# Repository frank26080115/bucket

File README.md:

Bucket
======

This is a tool made to transfer and backup photos from a professional camera while in-the-field. Built with a Raspberry Pi 4 (other Pis will work too, it's all just Python code), using Wi-Fi for file transfers and USB disks for file storage, powered by batteries.

The Problem
----

 While on photography trips, I'm running out of storage on my camera's memory cards. They are expensive memory cards and I can't buy too many of them ($400 for 160 GB, and the camera needs two). I don't want to go back to a hotel before clearing out a memory card either.

So the strategy is to wirelessly transfer the files into a cheaper-slower-but-bigger storage device (TB sized USB disks) simultaneously as the camera is shooting. The slower speed should be fine because the transfers will happen during the down-time, when I'm walking around not taking pictures. USB disks at this size typically cost just a bit over $100 (genuine, authentic, non-scam ones) and require USB-3.0 ports.

Once the photos are in the bigger storage device, I can clear the expensive-and-smaller memory cards without going back to a hotel, using in-camera quick-reformat.

This project needs to be done by late June of 2022, my next vacation. (I hope this explains some very weird decisions I've made)

Features
----

Runs as a FTP server for professional cameras to transfer photos into. A redundant copy of the photo is made if 2 USB disks are inserted. (most professional cameras have two card slots for the purpose of having redundancy as well)

Copies photos from SD card if a SD card reader is inserted into a USB port. Or plug in the camera itself (configure it to run in mass storage mode, and disable USB charging).

The file-names for the photos are typically numbered from 0 to 9999. This isn't a lot of photos and rolls over quickly. When a photo is copied, it is automatically renamed with a much longer number that indicates the date it was taken. The date makes every photo file-name unique and can be easily searched-for and sorted.

EXIF data of the photo is checked for the photo's 5-star rating, if it is rated in-camera, then it is automatically marked for keeping.

Performs disk-cloning when multiple USB disks are inserted.

Uses a HTTP server to show an image gallery in a web browser. The user can choose to keep or delete a photo from the web-page. Each photo is checked for where the camera focused on, and a zoomed-in cropped thumbnail is shown to the user showing where the camera focused (which is even cooler since my camera have AI driven bird-eye-detect).

This allows for a very quick decision whether or not an image is in-focus enough to keep. This implementation keeps the file-sizes small for the web-page, but the user can still click into the full resolution file too.

The software keeps track of the numbers in the file-names. If the number sequence skips a number, it might mean a missing photo, the missing number is shown to the user so they can check in the camera what happened. The camera can indicate a failed FTP transfer, but usually it just retries until it works. This is only useful when the camera is setup to transfer-as-you-shoot.

Hardware UX
----

The UI involves a 102x64 OLED screen and 5 buttons. It is very readable in all lighting conditions. The 5 buttons are divided into 2 up/down buttons and 3 action buttons.

The screen shows the most important information, such as the time (which is kind of like a heart-beat), the number of photos transferred, the amount of disk space remaining, etc.

There is a menu that can be accessed, the menu items are navigated with the up/down buttons. From the menu, the user can do things like initiate drive-cloning.

From the menu, the user can quickly check the Wi-Fi AP's credentials, the FTP IP address, and FTP credentials. It can also display the Wi-Fi credentials and HTTP URL as QR codes.

There is a buzzer that buzzes when there's a problem that requires the user's immediate attention, such as a disk running out of space, or if the battery is too low, etc. The user can press a button to acknowledge the problem to turn off the buzzer.

Hat Circuit and 3D Printed Box
----

This is the circuit I designed to go on top of the Raspberry Pi.

A 3D printed box is designed to protect the entire assembly. It is 3D printed in PETG plastic, because this whole thing gets super hot while running, PLA plastic just won't handle it.

The slots in the design are meant for strapping down a small USB SSD. These SSDs can have one or two TB of storage and should be pretty reliable since they use M.2 drives inside.

Software Architecture
----

This is just one massive Python project, spread across several modules. The hardware IO, various servers, and the main application, can all be independently tested. In fact, because Python is very cross-platform, I did most of my testing on Windows with a simulated screen.

The intention is to improve the reliability of this project by making the Raspberry Pi's microSD card read-only. The Python script will scan all mounted disks for a config file when it starts. This way, the user can still specify some parameters without ever writing to the microSD card.

The Python script will also log events and errors to the first available mounted disk.

The Python script is called upon by `/etc/rc.local`.

The library I used for the FTP server is [pyftpdlib](https://pypi.org/project/pyftpdlib/). The server class can be inherited, callback functions can be added, and a lot of the pathing functions had to be overridden.

The UI used a combination of [CircuitPython](https://circuitpython.org/) (and including the adafruit-circuitpython-ssd1306 library), [gpiozero](https://gpiozero.readthedocs.io/), and [Pillow](https://pillow.readthedocs.io/)

The HTTP server used Python's [built-in HTTP server library](https://docs.python.org/3/library/http.server.html). The HTML pages contains some [JQuery](https://jquery.com/) and uses lazy-loading images.

The EXIF related functions I borrowed [ExifTool](https://exiftool.org/), it's a Perl project but I call upon it as a subprocess from within Python.

USB disk auto-mounting is handled by [the usbmount Debian package](https://github.com/rbrito/usbmount/).

Threads
----

This device packs a bunch of features that involve IO against USB drives, and some of those tasks are more important. The software running has many threads that have multiple task queues with varying priorities.

The main thread is the GUI thread, which runs once every 0.2 seconds, giving a frame-rate of 5 FPS on the OLED display. Most of the thread time will be occupied by a very long I2C transaction as the frame-buffer is being sent to the OLED display. Other threads can run during this transfer without any penalty.

The FTP server and HTTP server both run on their own thread without any throttling, managed by their respective Python libraries. FTP is the most important thread. Wireless file transfer is the highest priority transfer, it isn't even queued, it happens immediately.

The other threads are started and stopped as needed: disk-cloner, keeper-copier, thumbnail-generator

The disk-cloner has two queues. The higher priority queue copies a recently wirelessly transferred file to the redundant disk. The lower priority queue copies between drives upon user request.

The keeper-copier slowly analyzes the EXIF data on recently transferred files to find their 5-star rating. Rated files are moved to the "keep" folder. These tasks has lower priority than the disk-cloner, but it also happens immediately if the user clicks the "keep" button on the HTTP server interface.

The thumbnail-generator thread is the lowest priority, but it becomes high priority when a HTTP client is accessing the thumbnails that have not been generating yet.

Power Supply
----

The hat circuit features a DC/DC step-down converter outputting 5V, rated for up to 6A. The input is supposed to come from two 8.4V batteries. The inputs are diode-OR'ed before going into the converter so I can swap one battery out without shutting down the Pi (and more importantly, prevents one battery literally exploding the other one). Each input is also connected to an ADC with a voltage divider in between.

As for the batteries, I decided it would be smart to use the same FZ100 batteries that my cameras use, so I can carry less stuff. I hacked up a dual charger for FZ100 batteries so it became a battery holder. It will still charge the batteries too.

A latching beefy connector is placed on the bottom of the charger, and wired to the battery tabs of the charger. On the Pi's hat is the mating connector.

This charger is attached to the bottom of the Raspberry Pi via LEGO!

I think this whole project draws about under 1A during actual file transfer using USB flash drives, but a bit over 1A when I use a USB-C SSD. Roughly 4 to 5 hours of battery life.

Alternative Implementation
----

The Raspberry Pi 4 is absolutely horrible for a battery powered project, it has zero power saving features, there's no sleep mode, and draws a ton of current even if the whole CPU is halted. This whole project would've made a lot more sense if it was just a smartphone app.

But my phone doesn't have nearly enough internal storage for this project, the USB port on my phone is also very suspect and I don't want to have a USB hub inserted into it during hikes. I recently did a battery swap on my phone because I love it so much and want to use it for a few more years. So I hope you understand why I can't justify buying a 1 terabyte Galaxy S22 Ultra for this project.

I am interested in an Android app implementation of this device though. Contact me if you want to chat about it.

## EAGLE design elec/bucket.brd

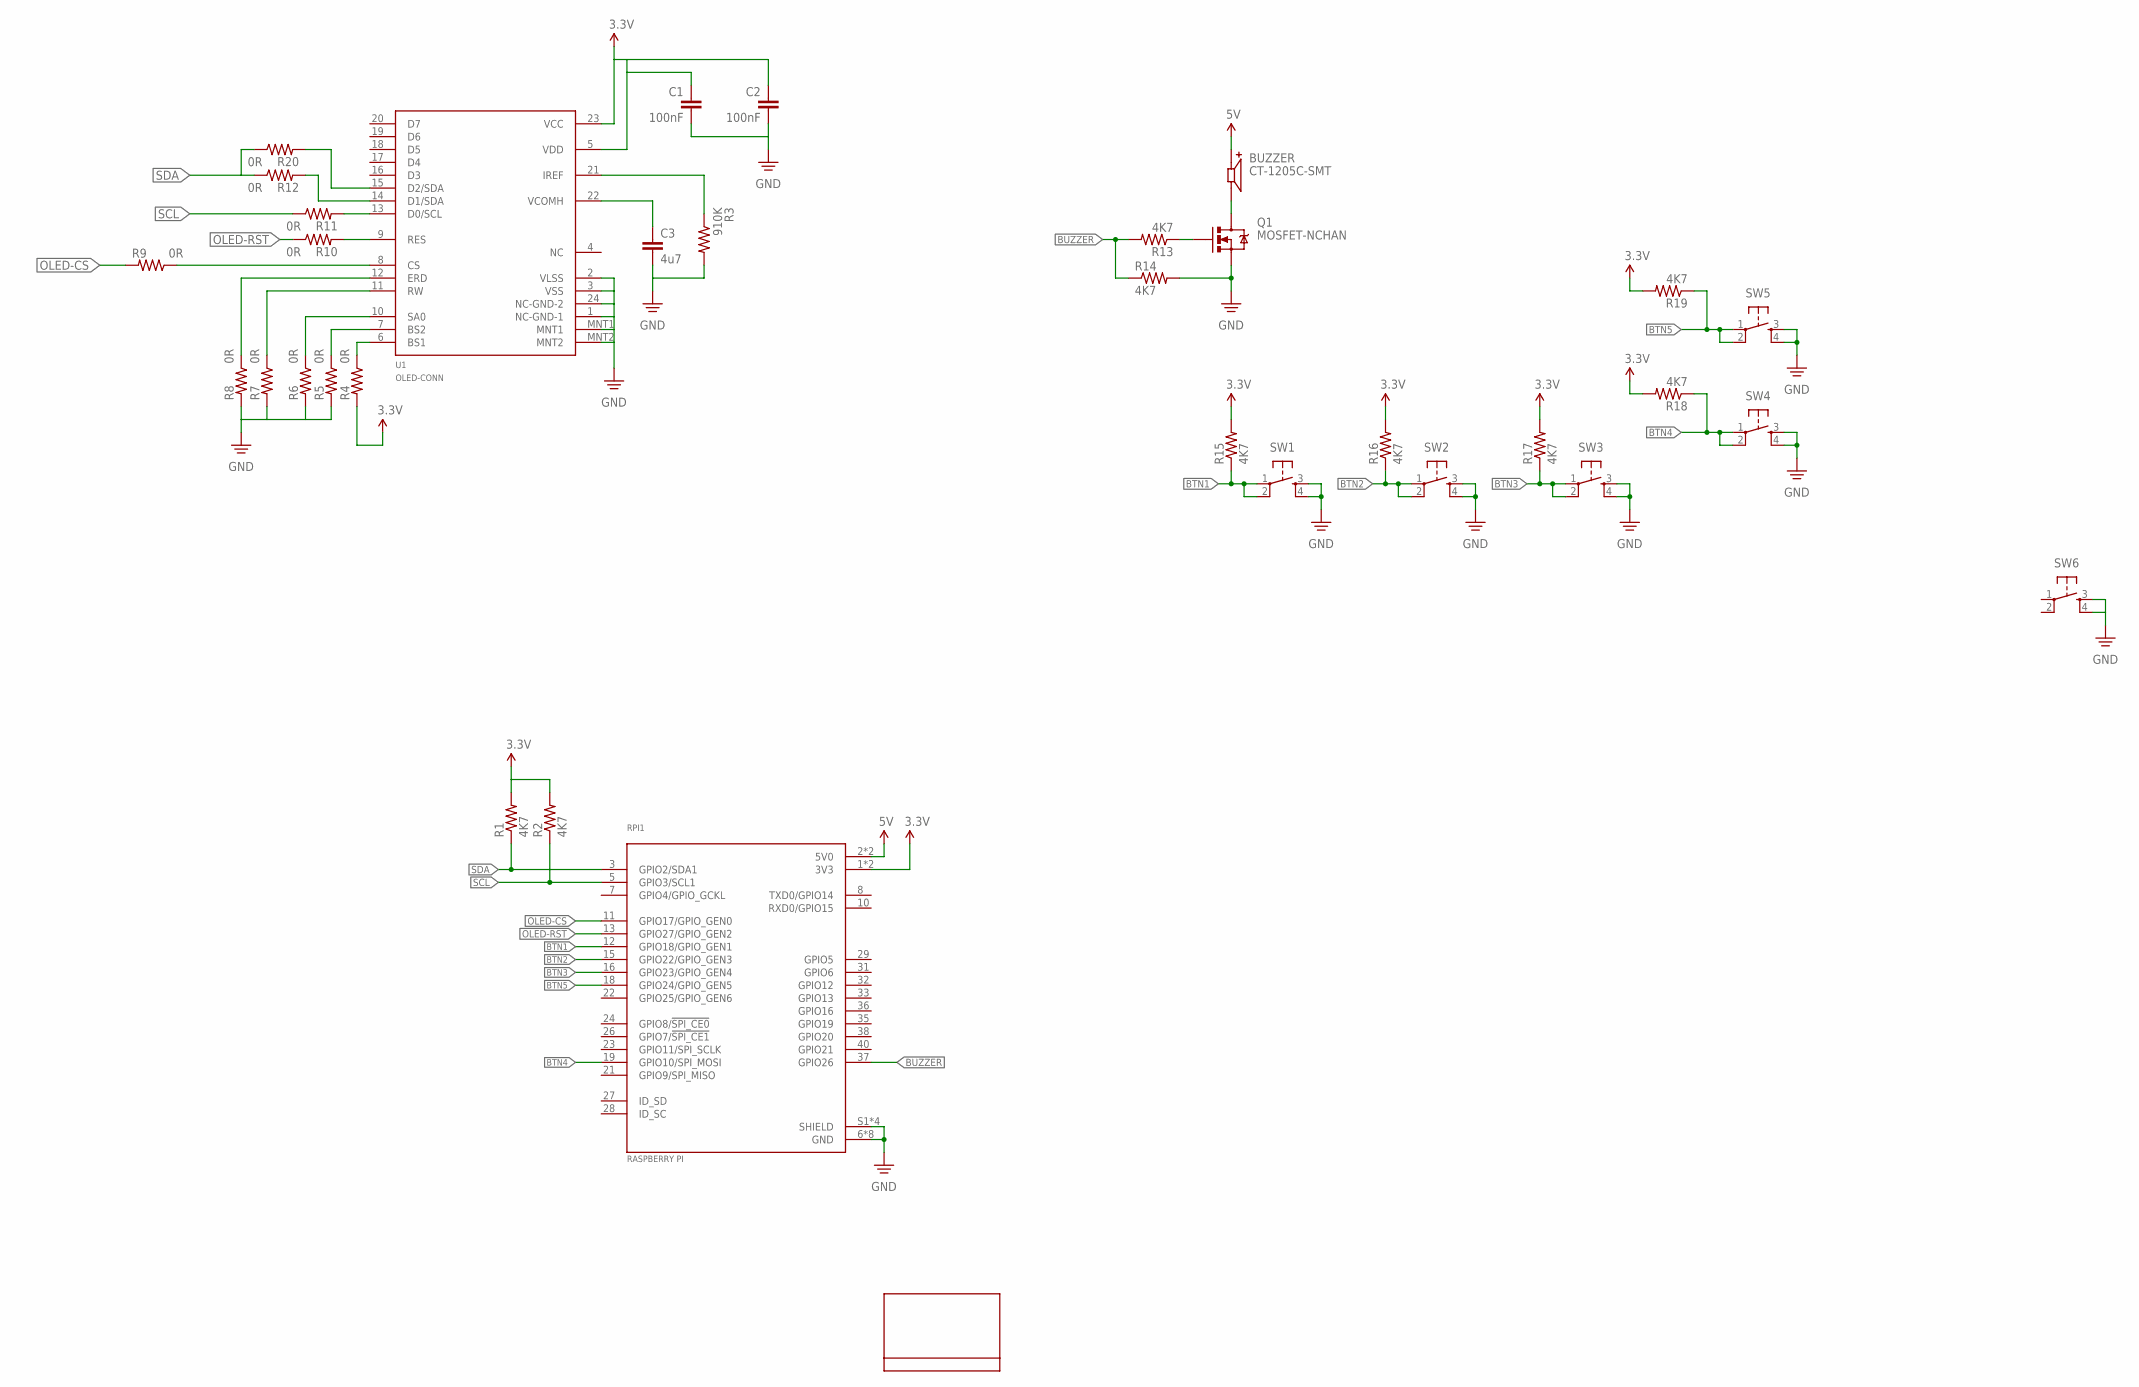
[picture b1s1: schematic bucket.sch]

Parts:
BUZZER: CT-1205C-SMT; CUI_CT-1205C-SMT
C1, C2: 100nF; 0603-CAP
C3: 4u7; 0603-CAP
Q1: MOSFET-NCHAN; SOT23-3
R1, R2, R13, R14, R15, R16, R17, R18, R19: 4K7; 0603-RES
R3: 910K; 0603-RES
R4, R5, R6, R7, R8, R9, R10, R11, R12, R20: 0R; 0603-RES
RPI1: RASPBERRY PI; MODULE_RASPBERRY_PI_3_MODEL_B+
SW1, SW2, SW3, SW4, SW5, SW6: TAC_SWITCHPTH; TACTILE-PTH
U1: OLED-CONN; CONN24_1X24_DRC_FFC_HIR
U$1: OLED-PANEL-1.54IN; OLED-1.54IN

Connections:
3.3V: C1.1, C2.1, R1.2, R2.2, R4.2, R15.2, R16.2, R17.2, R18.2, R19.2, RPI1.1 (3V3), RPI1.17 (3V3), U1.5 (VDD), U1.23 (VCC)
5V: BUZZER.1, RPI1.2 (5V0), RPI1.4 (5V0)
BTN1: R15.1, RPI1.12 (GPIO18/GPIO_GEN1), SW1.1, SW1.2
BTN2: R16.1, RPI1.15 (GPIO22/GPIO_GEN3), SW2.1, SW2.2
BTN3: R17.1, RPI1.16 (GPIO23/GPIO_GEN4), SW3.1, SW3.2
BTN4: R18.1, RPI1.19 (GPIO10/SPI_MOSI), SW4.1, SW4.2
BTN5: R19.1, RPI1.18 (GPIO24/GPIO_GEN5), SW5.1, SW5.2
BUZZER: R13.2, R14.1, RPI1.37 (GPIO26)
GND: C1.2, C2.2, C3.2, Q1.2 (S), R3.2, R5.2, R6.2, R7.2, R8.2, R14.2, RPI1.6 (GND), RPI1.9 (GND), RPI1.14 (GND), RPI1.20 (GND), RPI1.25 (GND), RPI1.30 (GND), RPI1.34 (GND), RPI1.39 (GND), RPI1.S1 (SHIELD), RPI1.S2 (SHIELD), RPI1.S3 (SHIELD), RPI1.S4 (SHIELD), SW1.3, SW1.4, SW2.3, SW2.4, SW3.3, SW3.4, SW4.3, SW4.4, SW5.3, SW5.4, SW6.3, SW6.4, U1.1 (NC-GND-1), U1.2 (VLSS), U1.3 (VSS), U1.24 (NC-GND-2), U1.MNT1, U1.MNT2
unnamed: C3.1, U1.22 (VCOMH)
unnamed: R3.1, U1.21 (IREF)
unnamed: R4.1, U1.6 (BS1)
unnamed: R5.1, U1.7 (BS2)
unnamed: Q1.1 (G), R13.1
unnamed: BUZZER.2, Q1.3 (D)
unnamed: R6.1, U1.10 (SA0)
unnamed: R7.1, U1.11 (RW)
unnamed: R8.1, U1.12 (ERD)
unnamed: R9.1, U1.8 (CS)
unnamed: R10.2, U1.9 (RES)
unnamed: R11.2, U1.13 (D0/SCL)
unnamed: R12.2, U1.14 (D1/SDA)
unnamed: R20.2, U1.15 (D2/SDA)
OLED-CS: R9.2, RPI1.11 (GPIO17/GPIO_GEN0)
OLED-RST: R10.1, RPI1.13 (GPIO27/GPIO_GEN2)
SCL: R2.1, R11.1, RPI1.5 (GPIO3/SCL1)
SDA: R1.1, R12.1, R20.1, RPI1.3 (GPIO2/SDA1)

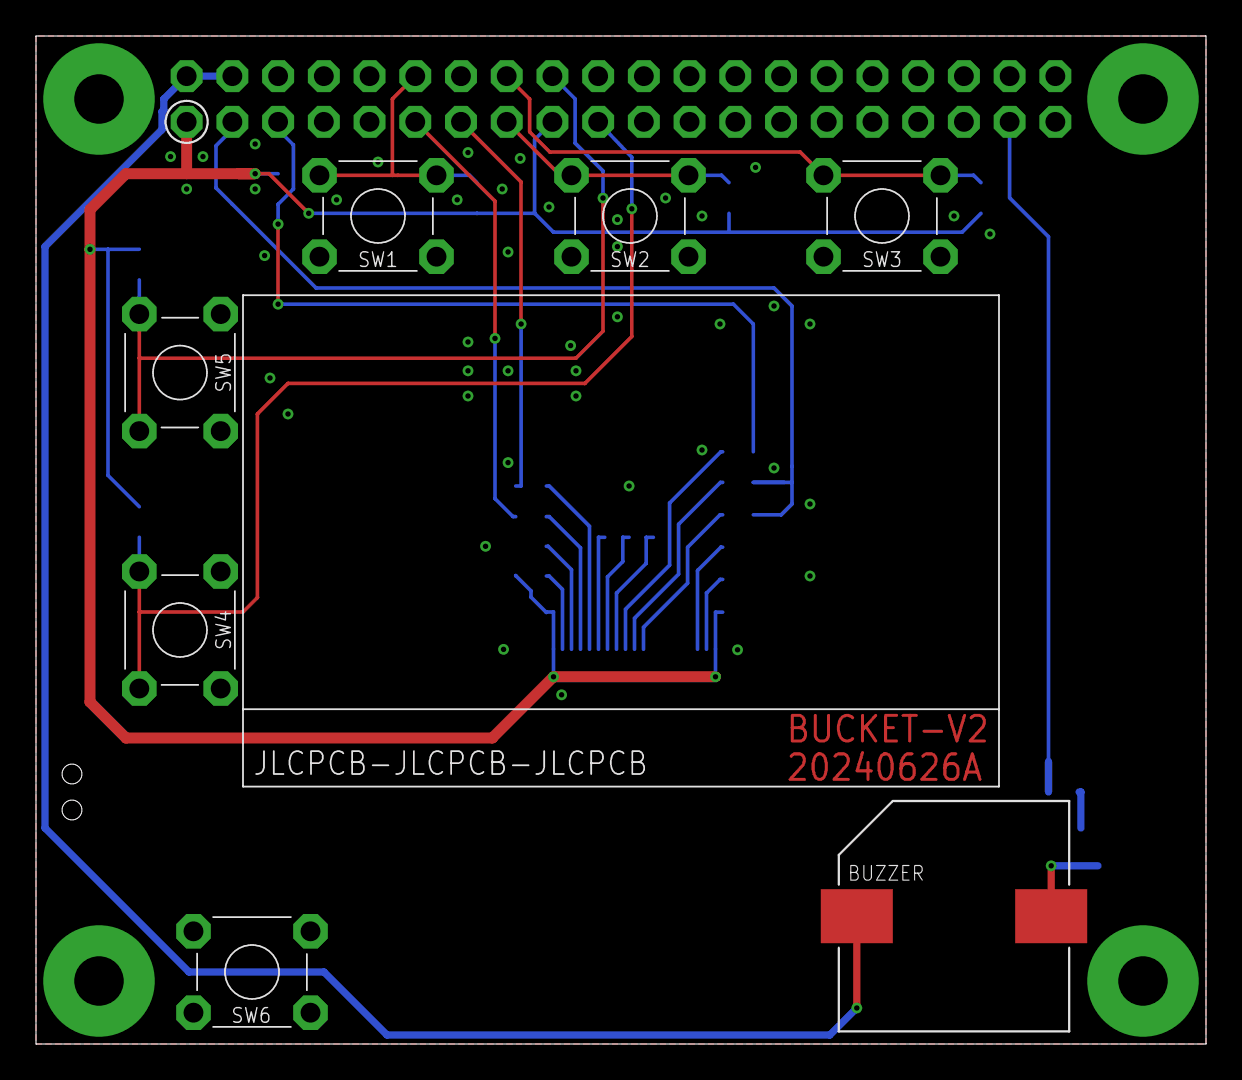
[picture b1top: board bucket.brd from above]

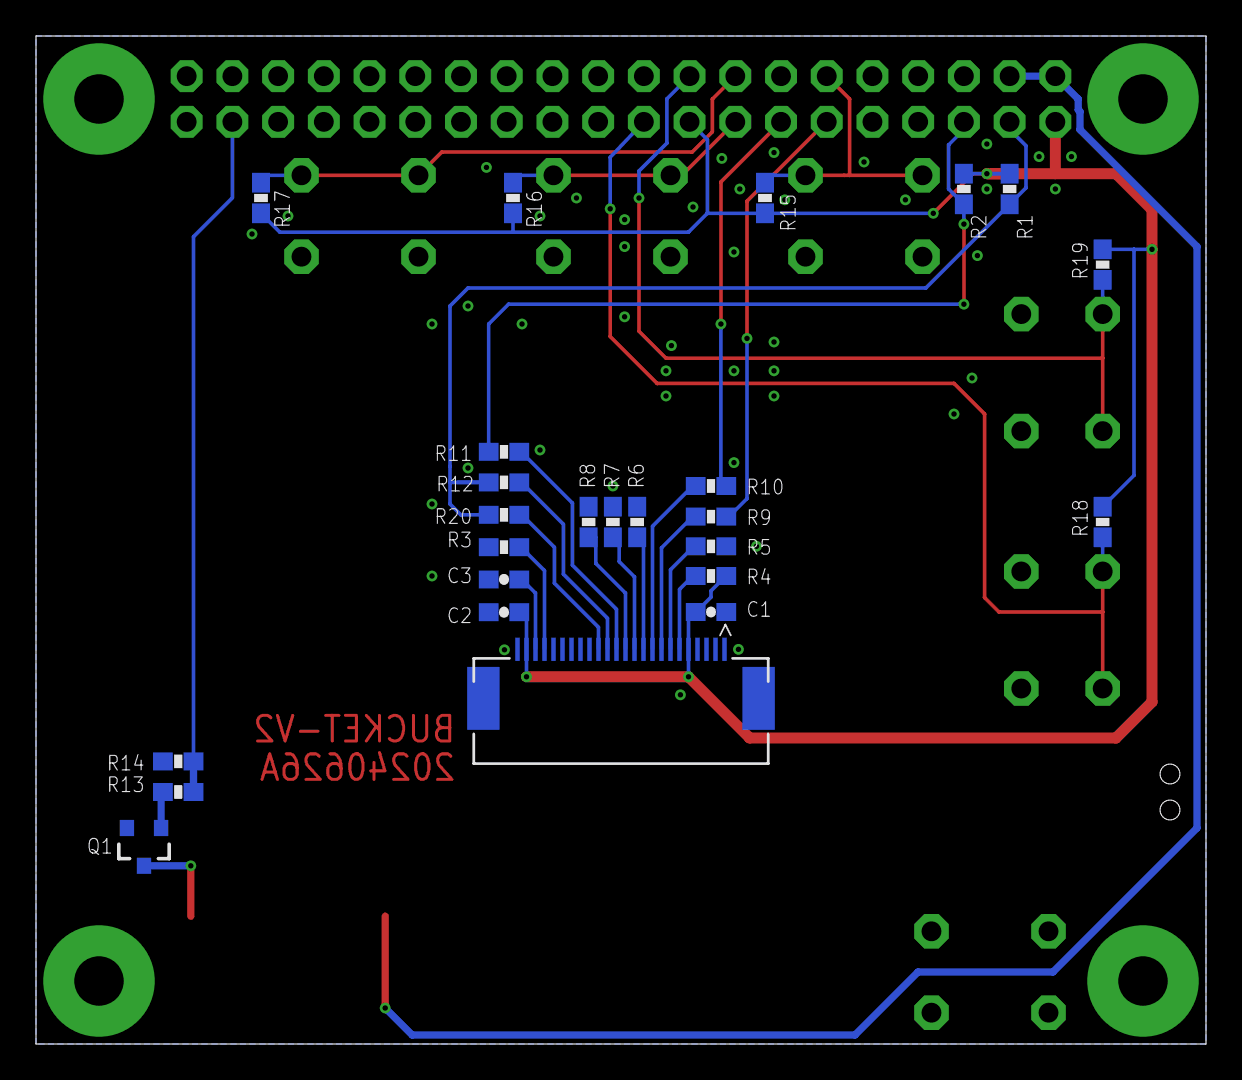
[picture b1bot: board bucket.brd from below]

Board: 2 copper layers, 65.0 x 56.0 mm, 34 parts (25 on the bottom side), 27 nets.

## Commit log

2022-05-06 parts for circuit, day 1
2022-05-07 major progress on circuit design
2022-05-08 circuit first rev finished and gerbers sent to manufacture
2022-05-08 circuit schematic as image
2022-05-08 upload some datasheets of components
2022-05-09 progress on python code
2022-05-09 python code progress day 2 morning
2022-05-11 python code progress, can run FTP and sim UI
2022-05-12 major python code progress, FTP tested, more app work
2022-05-13 adding a http server to view and cull photos
2022-05-15 code more work on cloning/copying
2022-05-16 started mech design of 3D printed case
2022-05-17 mech updates, corrected for standoff height and screw size
2022-05-17 code work in progress
2022-05-17 getting ready to do some basic tests on a real pi
2022-05-17 tested bucketio on real hardware
    ADC definitely not reading right, needs calibration, also can't detect removed battery
    OLED working
    Buttons working but can't trust the "held" function
    Buzzer not making a sound
2022-05-18 code work in progress, added cpu scaling, plus more improvements
2022-05-18 mech changes to 3D printed box, added holes for LEDs, etc
2022-05-18 adc calibration
2022-05-22 added get_wifi_clients to code
2022-05-22 code syntax fixes before running in simulation
2022-05-22 code improvements after running on pi
2022-05-23 code can copy from SD, rename, generate thumbs, and other improvements
2022-05-24 code FTP working, fixed memory leaks, fixed lost file miscounting
2022-05-24 code, got http server working
2022-05-25 code fixed a bunch of linux-only bugs
2022-05-25 slightly more sane fix for failed path joining
2022-05-25 code more fixes for bugs found on pi
2022-05-30 mech changes, printed and assembled
2022-05-30 documentation photographs
2022-05-30 code changes, mainly UI stuff, added QR code
2022-05-30 improved QR code implemen, added wifi credentials
2022-05-31 more ui refinement, added demo screen
2022-05-31 readme updates
2022-05-31 readme update
2022-05-31 picture was wayyyyy too big
2022-05-31 update documentation
2022-06-05 added buttons to mass delete
2024-06-27 PCB v2
2024-06-27 new mech for new version
